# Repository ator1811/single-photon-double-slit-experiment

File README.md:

# single photon double-slit-experiment
Dutch repository to use the Single photon double slit experiment of the University of Twente

Next to software a number of articles are included to provide didactial approaches.

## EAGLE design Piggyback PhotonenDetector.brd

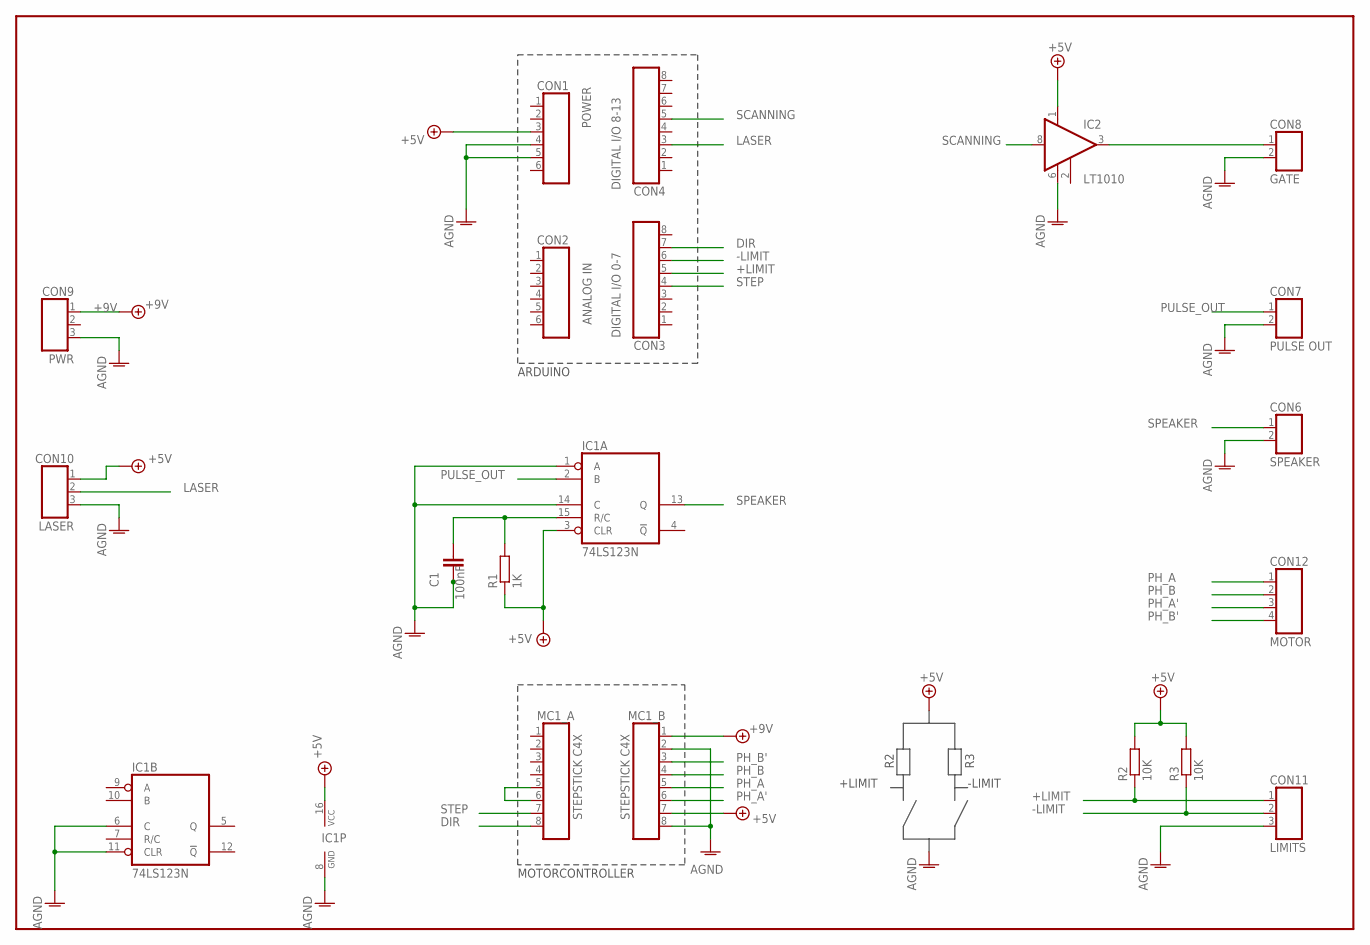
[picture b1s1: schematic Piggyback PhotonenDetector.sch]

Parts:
C1: 100nF; C025_050-025X075
CON1: POWER; HDR-06-2.54
CON2: ANALOG IN; HDR-06-2.54
CON3: DIGITAL I/O 0-7; HDR-08-2.54
CON4: DIGITAL I/O 8-13; HDR-08-2.54
CON6: SPEAKER; HDR-02-2.54
CON7: PULSE OUT; HDR-02-2.54
CON8: GATE; HDR-02-2.54
CON9: PWR; HDR-03-2.54
CON10: LASER; HDR-03-2.54
CON11: LIMITS; HDR-03-2.54
CON12: MOTOR; HDR-04-2.54
IC1: 74LS123N; DIL16
IC2: LT1010; DIL08
MC1_A, MC1_B: STEPSTICK C4X; HDR-08-2.54
R1: 1K; 0207/10
R2, R3: 10K; 0207/10

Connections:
+5V: CON1.3, CON10.1, IC1.3 (CLR), IC1.16 (VCC), IC2.1 (V+), MC1_B.7, R1.1, R2.2, R3.2
+9V: CON9.1, MC1_B.1
+LIMIT: CON3.5, CON11.1, R2.1
-LIMIT: CON3.6, CON11.2, R3.1
AGND: C1.2, C1.3, CON1.4, CON1.5, CON6.2, CON7.2, CON8.2, CON9.3, CON10.3, CON11.3, IC1.1 (A), IC1.6 (C), IC1.8 (GND), IC1.11 (CLR), IC1.14 (C), IC2.6 (V-), MC1_B.2, MC1_B.8
DIR: CON3.7, MC1_A.8
LASER: CON4.3, CON10.2
unnamed: C1.1, IC1.15 (R/C), R1.2
unnamed: MC1_A.5, MC1_A.6
unnamed: CON8.1, IC2.3 (OUT)
PH_A: CON12.1, MC1_B.5
PH_A': CON12.3, MC1_B.6
PH_B: CON12.2, MC1_B.4
PH_B': CON12.4, MC1_B.3
PULSE_OUT: CON7.1, IC1.2 (B)
SCANNING: CON4.5, IC2.8 (+IN)
SPEAKER: CON6.1, IC1.13 (Q)
STEP: CON3.4, MC1_A.7

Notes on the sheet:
ARDUINO
MOTORCONTROLLER
+LIMIT
-LIMIT

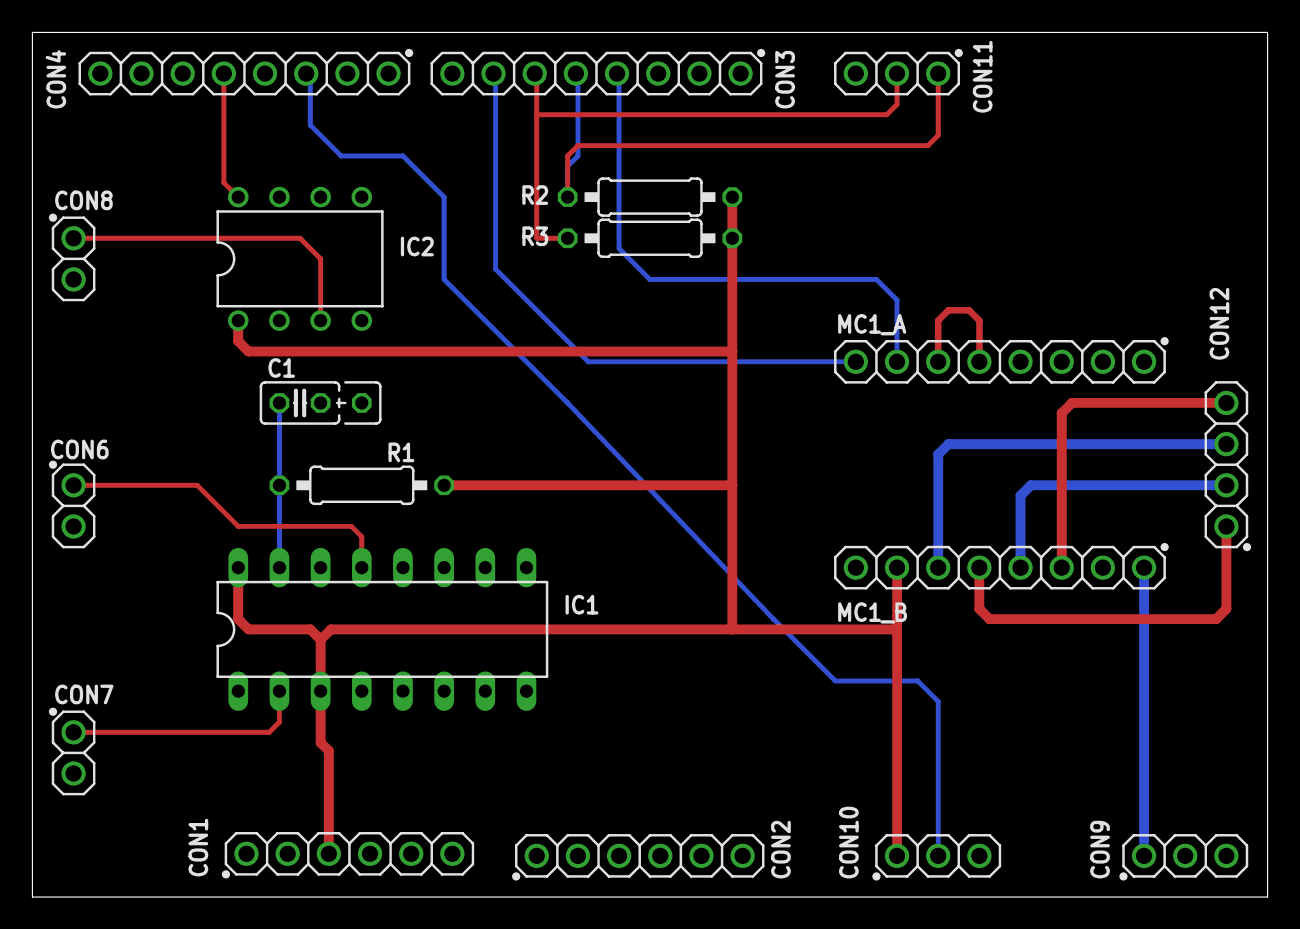
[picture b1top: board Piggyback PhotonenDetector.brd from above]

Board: 2 copper layers, 76.2 x 53.3 mm, 19 parts (0 on the bottom side), 18 nets.

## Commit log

2019-05-08 Create lazy_bottom_mount.stl
    added for test
2019-05-09 new file
2024-11-24 Initial upload
    from public Dropbox
2024-11-24 initial upload prt ii
